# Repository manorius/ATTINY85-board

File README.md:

# ATTINY85-board
V-USB ATTINY BOARD based on Digispark schematic https://s3.amazonaws.com/digistump-resources/files/97a1bb28_DigisparkSchematic.pdf

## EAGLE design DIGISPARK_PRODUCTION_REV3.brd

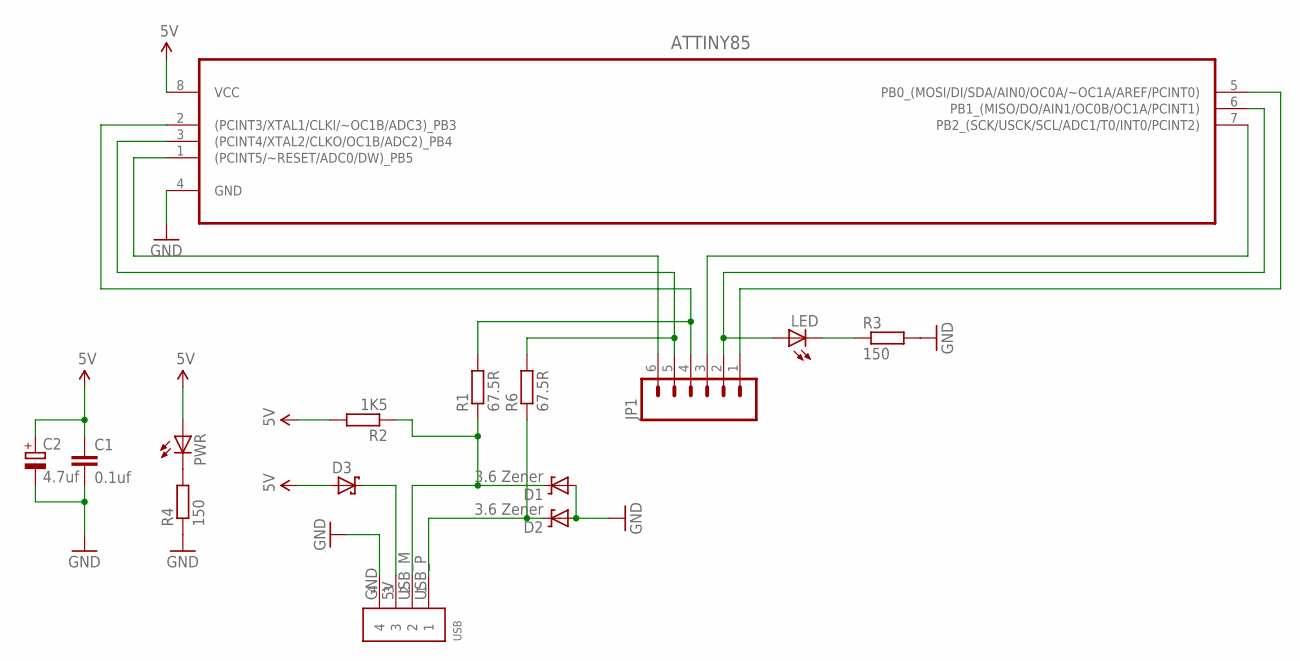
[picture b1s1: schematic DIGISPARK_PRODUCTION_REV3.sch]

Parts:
ATTINY85: ATTINY85-20PU; DIP254P762X533-8
C1: 0.1uf; C050-045X075
C2: 4.7uf; E5-4
D1, D2: 3.6 Zener; DIODE-ZENER
D3: SCHOTTKY-DIODEDO35-7; DO35-7
JP1: M06SIP; 1X06
LED: LED5MM
PWR: LED5MM
R1, R6: 67.5R; 0207/12
R2: 1K5; 0207/12
R3, R4: 150; 0207/12
USB: 1X4-CLEANBIG; 1X04-CLEANBIG

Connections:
5V: ATTINY85.8 (VCC), C1.1, C2.+, D3.A, PWR.A, R2.2
GND: ATTINY85.4 (GND), C1.2, C2.-, D1.P$2 (A), D2.P$2 (A), R3.2, R4.1, USB.4
unnamed: PWR.K (C), R4.2
unnamed: ATTINY85.6 (PB1_(MISO/DO/AIN1/OC0B/OC1A/PCINT1)), JP1.2, LED.A
unnamed: LED.K (C), R3.1
unnamed: ATTINY85.1 ((PCINT5/~RESET/ADC0/DW)_PB5), JP1.6
unnamed: D1.P$1 (C), R1.1, R2.1, USB.2
unnamed: D2.P$1 (C), R6.1, USB.1
unnamed: ATTINY85.2 ((PCINT3/XTAL1/CLKI/~OC1B/ADC3)_PB3), JP1.4, R1.2
unnamed: ATTINY85.7 (PB2_(SCK/USCK/SCL/ADC1/T0/INT0/PCINT2)), JP1.3
unnamed: ATTINY85.3 ((PCINT4/XTAL2/CLKO/OC1B/ADC2)_PB4), JP1.5, R6.2
unnamed: D3.C, USB.3
unnamed: ATTINY85.5 (PB0_(MOSI/DI/SDA/AIN0/OC0A/~OC1A/AREF/P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), JP1.1

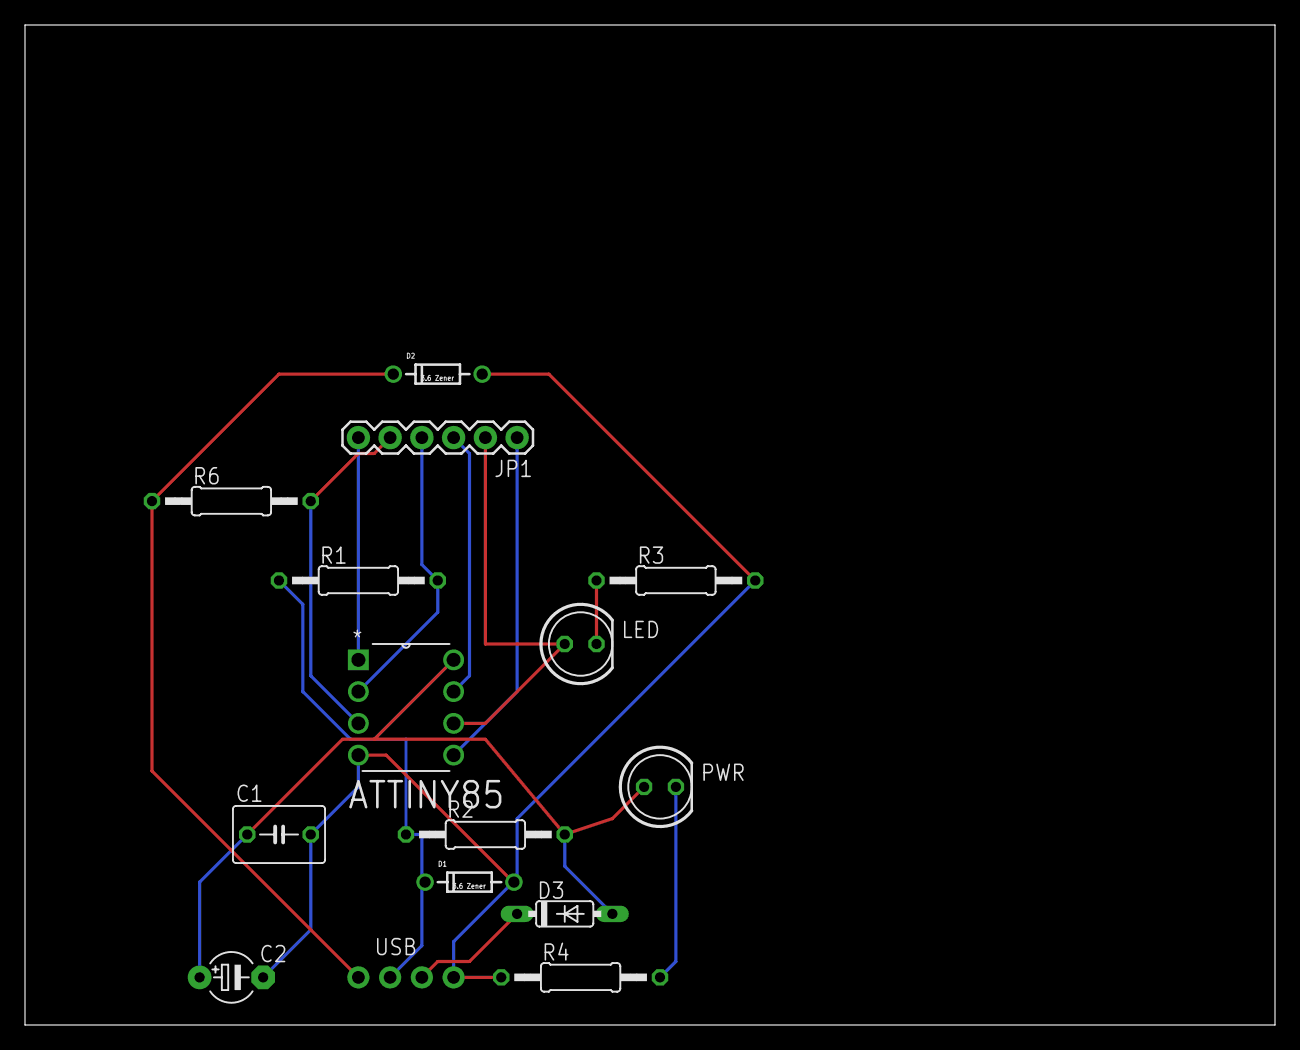
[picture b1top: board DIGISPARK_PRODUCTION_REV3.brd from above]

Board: 2 copper layers, 100.0 x 80.0 mm, 15 parts (0 on the bottom side), 13 nets.

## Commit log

2017-01-25 init commit
2017-01-26 new schematic added with to pin connectors along with PCB design
2017-02-03 latest illustlustrator vectors added
2017-02-03 thicker lines
2017-02-03 even thicker lines

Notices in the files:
parts and their libraries:
SparkFun: Licensing: CC v3.0 Share-Alike You are welcome to use this library for commercial purposes.
